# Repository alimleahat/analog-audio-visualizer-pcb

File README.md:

# Analog Audio Visualizer PCB

A three-band audio visualizer built for **ELEC2101 Electronic Circuits and Systems Design**. It separates audio into bass, midrange, and treble, with an LED responding to each band.

## My contribution

Following the course guide and reference circuit, I completed the schematic in KiCad, assigned component footprints, laid out and routed the PCB, prepared the manufacturing files, assembled the board, and tested it in the lab.

The project gave me practical experience with analog circuits, two-layer PCB layout, through-hole and surface-mount soldering, and electrical measurements.

## How it works

The audio input passes through an adjustable amplifier, then three filters separate the low, middle, and high frequencies. Transistor circuits drive the corresponding LEDs. The circuit uses LM2904 and LM2902 op-amps and a dual ±12 V supply.

[View the schematic](docs/images/schematic.png) · [View the PCB layout](docs/images/pcb-layout.png)

## Assembly and testing

The board was assembled and tested using a regulated bench supply connected through J3. The recorded supply measurements were **+11.99 V** and **−12.03 V**. The lab checklist records all three LEDs responding to audio and the sensitivity adjustment working.

The bridge rectifier BR1 was unavailable, so the AC-input power-supply section was not tested. The treble LED is yellow instead of the blue LED specified in the design.

[Solder-side photo](docs/images/solder-side.png) · [Surface-mount detail](docs/images/smd-detail.png) · [Measurement photos and test notes](docs/testing.md)

## Open the design

Open [`hardware/audiovisualiser.kicad_pro`](hardware/audiovisualiser.kicad_pro) in **KiCad 9** with the standard symbol and footprint libraries installed. The project includes the editable schematic and PCB layout.

The folders contain:

- **`hardware/`** — KiCad project, schematic, and PCB.
- **`manufacturing/`** — Gerber and drill files for fabrication, a bill of materials, and component positions.
- **`docs/`** — design images, assembly photos, measurements, and design-check reports.

The latest KiCad checks report no electrical or PCB layout violations under the saved rules, and no unconnected items. Four comparison warnings identify mounting holes that appear only on the PCB. Details are in the [testing notes](docs/testing.md).

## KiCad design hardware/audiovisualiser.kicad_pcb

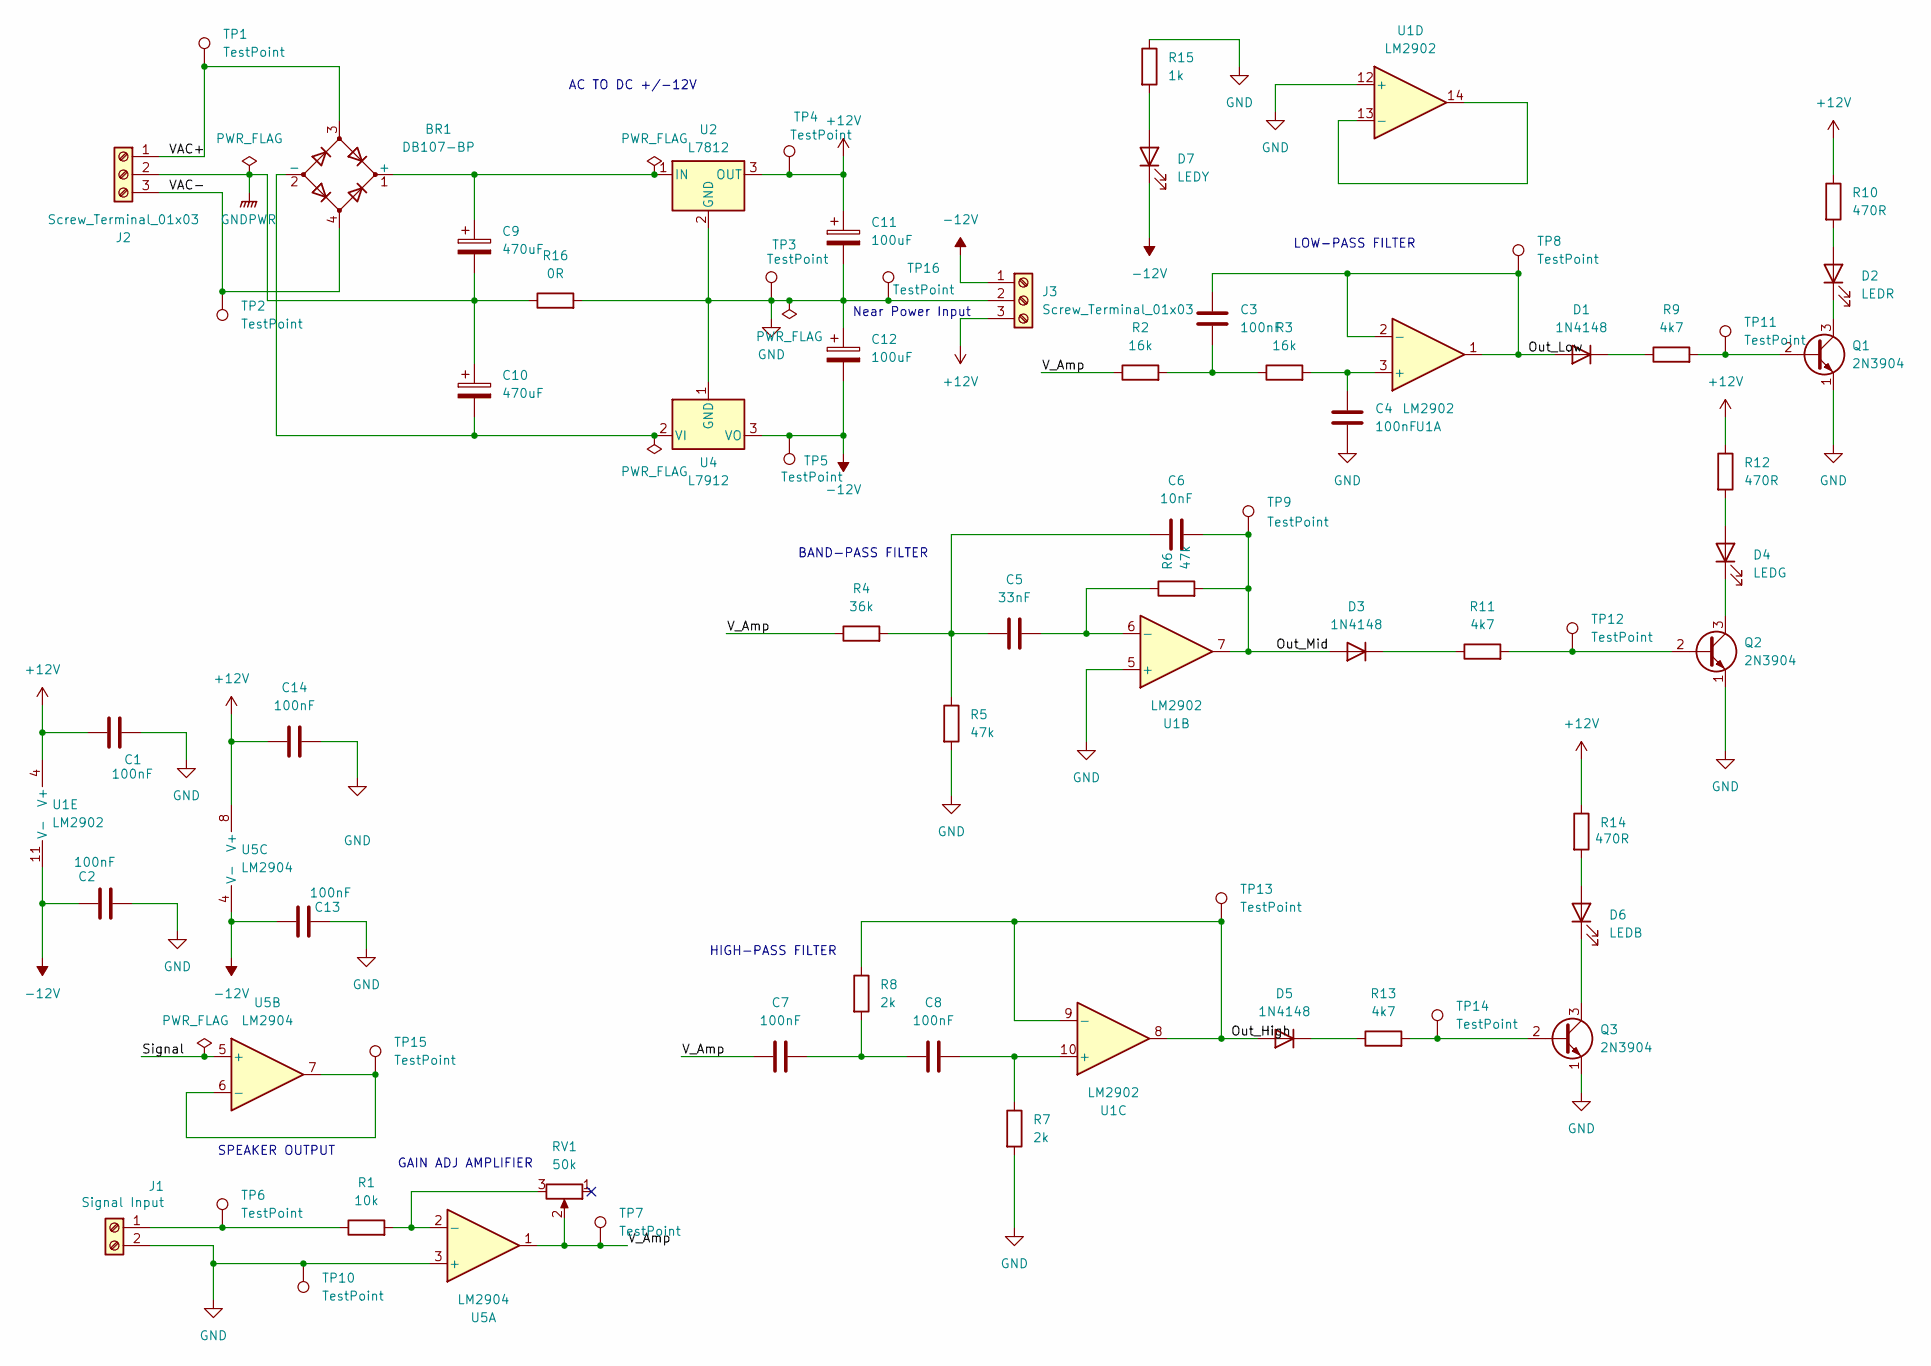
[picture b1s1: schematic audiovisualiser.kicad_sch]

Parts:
BR1: DB107-BP; Diode_Bridge_DIP-4_W7.62mm_P5.08mm
C1, C2, C3, C4, C7, C8, C13, C14: 100nF; C_Rect_L7.0mm_W2.5mm_P5.00mm
C5: 33nF; C_Rect_L7.0mm_W2.5mm_P5.00mm
C6: 10nF; C_Rect_L7.0mm_W2.5mm_P5.00mm
C9, C10: 470uF; CP_Radial_D8.0mm_P3.50mm
C11, C12: 100uF; CP_Radial_D8.0mm_P3.50mm
D1, D3, D5: 1N4148; D_DO-35_SOD27_P7.62mm_Horizontal
D2: LEDR; LED_D3.0mm
D4: LEDG; LED_D3.0mm
D6: LEDB; LED_D3.0mm
D7: LEDY; LED_D3.0mm
J1: Signal Input; TerminalBlock_Phoenix_MKDS-1,5-2-5.08_1x02_P5.08mm_Horizont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
J2, J3: Screw_Terminal_01x03; TerminalBlock_Phoenix_MKDS-1,5-3-5.08_1x03_P5.08mm_Horizont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
Q1, Q2, Q3: 2N3904; TO-92_Inline
R1: 10k; R_Axial_DIN0207_L6.3mm_D2.5mm_P10.16mm_Horizontal
R2, R3: 16k; R_Axial_DIN0207_L6.3mm_D2.5mm_P10.16mm_Horizontal
R4: 36k; R_Axial_DIN0207_L6.3mm_D2.5mm_P10.16mm_Horizontal
R5, R6: 47k; R_Axial_DIN0207_L6.3mm_D2.5mm_P10.16mm_Horizontal
R7, R8: 2k; R_Axial_DIN0207_L6.3mm_D2.5mm_P10.16mm_Horizontal
R9, R11, R13: 4k7; R_2512_6332Metric
R10, R12, R14: 470R; R_2512_6332Metric
R15: 1k; R_Axial_DIN0207_L6.3mm_D2.5mm_P10.16mm_Horizontal
R16: 0R; R_2512_6332Metric
RV1: 50k; Potentiometer_Bourns_3299W_Vertical
TP1, TP2, TP3, TP4, TP5, TP6, TP7, TP8, TP9, TP10, TP11, TP12, TP13, TP14, TP15, TP16: TestPoint; PinHeader_1x01_P2.54mm_Vertical
U1: LM2902; DIP-14_W7.62mm
U2: L7812; TO-220-3_Vertical
U4: L7912; TO-220-3_Vertical
U5: LM2904; DIP-8_W7.62mm

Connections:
+12V: C1.2, C11.1, C14.1, J3.3, R10.1, R12.1, R14.1, TP4.1, U1.4 (V+), U2.3 (OUT), U5.8 (V+)
-12V: C2.1, C12.2, C13.1, D7.1 (K), J3.1, TP5.1, U1.11 (V-), U4.3 (VO), U5.4 (V-)
/Out_High: D5.2 (A), R8.1, TP13.1, U1.8, U1.9 (-)
/Out_Low: C3.1, D1.2 (A), TP8.1, U1.1, U1.2 (-)
/Out_Mid: C6.2, D3.2 (A), R6.2, TP9.1, U1.7
/Signal: U5.5 (+)
/VAC+: BR1.3, J2.1, TP1.1
/VAC-: BR1.4, J2.3, TP2.1
/V_Amp: C7.1, R2.1, R4.1, RV1.2, TP7.1, U5.1
GND: C1.1, C2.2, C4.2, C11.2, C12.1, C13.2, C14.2, J1.2, J3.2, Q1.1 (E), Q2.1 (E), Q3.1 (E), R5.2, R7.2, R15.1, R16.2, TP3.1, TP10.1, TP16.1, U1.5 (+), U1.12 (+), U2.2 (GND), U4.1 (GND), U5.3 (+)
GNDPWR: C9.2, C10.1, J2.2, R16.1
unnamed: BR1.1 (+), C9.1, U2.1 (IN)
unnamed: BR1.2 (-), C10.2, U4.2 (VI)
unnamed: C3.2, R2.2, R3.1
unnamed: C5.1, C6.1, R4.2, R5.1
unnamed: C7.2, C8.1, R8.2
unnamed: D1.1 (K), R9.1
unnamed: D2.2 (A), R10.2
unnamed: D2.1 (K), Q1.3 (C)
unnamed: D3.1 (K), R11.1
unnamed: D4.2 (A), R12.2
unnamed: D4.1 (K), Q2.3 (C)
unnamed: D5.1 (K), R13.1
unnamed: D6.2 (A), R14.2
unnamed: D6.1 (K), Q3.3 (C)
unnamed: D7.2 (A), R15.2
unnamed: J1.1, R1.1, TP6.1
unnamed: Q1.2 (B), R9.2, TP11.1
unnamed: Q2.2 (B), R11.2, TP12.1
unnamed: Q3.2 (B), R13.2, TP14.1
unnamed: C4.1, R3.2, U1.3 (+)
unnamed: C5.2, R6.1, U1.6 (-)
unnamed: C8.2, R7.1, U1.10 (+)
unnamed: U1.13 (-), U1.14
unnamed: R1.2, RV1.3, U5.2 (-)
unnamed: TP15.1, U5.6 (-), U5.7

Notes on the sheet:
SPEAKER OUTPUT
Near Power Input
GAIN ADJ AMPLIFIER
AC TO DC +/-12V
HIGH-PASS FILTER
BAND-PASS FILTER
LOW-PASS FILTER

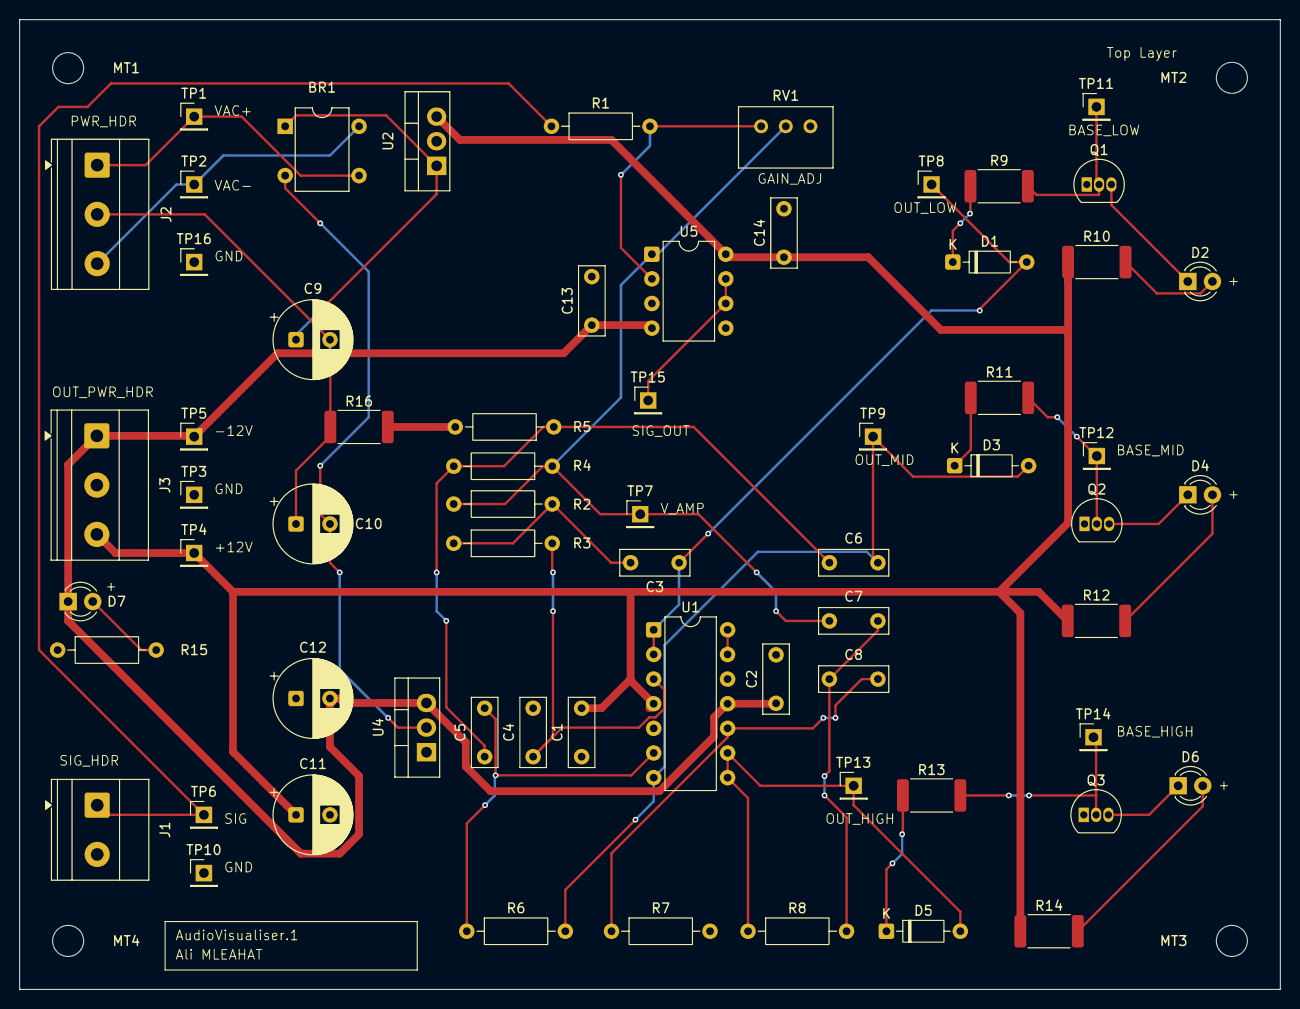
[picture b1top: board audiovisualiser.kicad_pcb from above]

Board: 2 copper layers, 130.0 x 100.0 mm, 69 parts (0 on the bottom side), 35 nets.

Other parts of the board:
MT1, MT2, MT3, MT4: MountingHole_3.2mm_M3

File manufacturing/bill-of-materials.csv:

"Reference","Qty","Value","Footprint"
"BR1","1","DB107-BP","Diode_THT:Diode_Bridge_DIP-4_W7.62mm_P5.08mm"
"C1,C2,C3,C4,C7,C8,C13,C14","8","100nF","Capacitor_THT:C_Rect_L7.0mm_W2.5mm_P5.00mm"
"C5","1","33nF","Capacitor_THT:C_Rect_L7.0mm_W2.5mm_P5.00mm"
"C6","1","10nF","Capacitor_THT:C_Rect_L7.0mm_W2.5mm_P5.00mm"
"C9,C10","2","470uF","Capacitor_THT:CP_Radial_D8.0mm_P3.50mm"
"C11,C12","2","100uF","Capacitor_THT:CP_Radial_D8.0mm_P3.50mm"
"D1,D3,D5","3","1N4148","Diode_THT:D_DO-35_SOD27_P7.62mm_Horizontal"
"D2","1","LEDR","LED_THT:LED_D3.0mm"
"D4","1","LEDG","LED_THT:LED_D3.0mm"
"D6","1","LEDB","LED_THT:LED_D3.0mm"
"D7","1","LEDY","LED_THT:LED_D3.0mm"
"J1","1","Signal Input","TerminalBlock_Phoenix:TerminalBlock_Phoenix_MKDS-1,5-2-5.08_1x02_P5.08mm_Horizontal"
"J2,J3","2","Screw_Terminal_01x03","TerminalBlock_Phoenix:TerminalBlock_Phoenix_MKDS-1,5-3-5.08_1x03_P5.08mm_Horizontal"
"Q1,Q2,Q3","3","2N3904","Package_TO_SOT_THT:TO-92_Inline"
"R1","1","10k","Resistor_THT:R_Axial_DIN0207_L6.3mm_D2.5mm_P10.16mm_Horizontal"
"R2,R3","2","16k","Resistor_THT:R_Axial_DIN0207_L6.3mm_D2.5mm_P10.16mm_Horizontal"
"R4","1","36k","Resistor_THT:R_Axial_DIN0207_L6.3mm_D2.5mm_P10.16mm_Horizontal"
"R5,R6","2","47k","Resistor_THT:R_Axial_DIN0207_L6.3mm_D2.5mm_P10.16mm_Horizontal"
"R7,R8","2","2k","Resistor_THT:R_Axial_DIN0207_L6.3mm_D2.5mm_P10.16mm_Horizontal"
"R9,R11,R13","3","4k7","Resistor_SMD:R_2512_6332Metric"
"R10,R12,R14","3","470R","Resistor_SMD:R_2512_6332Metric"
"R15","1","1k","Resistor_THT:R_Axial_DIN0207_L6.3mm_D2.5mm_P10.16mm_Horizontal"
"R16","1","0R","Resistor_SMD:R_2512_6332Metric"
"RV1","1","50k","Potentiometer_THT:Potentiometer_Bourns_3299W_Vertical"
"TP1,TP2,TP3,TP4,TP5,TP6,TP7,TP8,TP9,TP10,TP11,TP12,TP13,TP14,TP15,TP16","16","TestPoint","Connector_PinHeader_2.54mm:PinHeader_1x01_P2.54mm_Vertical"
"U1","1","LM2902","Package_DIP:DIP-14_W7.62mm"
"U2","1","L7812","Package_TO_SOT_THT:TO-220-3_Vertical"
"U4","1","L7912","Package_TO_SOT_THT:TO-220-3_Vertical"
"U5","1","LM2904","Package_DIP:DIP-8_W7.62mm"
